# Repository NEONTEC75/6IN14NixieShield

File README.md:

# 6IN14NixieShield
This shield is just a minimal Nixie multiplexed circuit and contains the following components:
- 74141 nixie cathode driver IC (pins 4, 6, 7, 5);
- TLP627 opto-couplers for anodes (pins 12, 11, 9, 8, A1, A2, and pin 10 for the dots);
- 3-button resistive keyboard (A3);
- simple boost converter driven by Arduino's PWM (pin 3, and pin A0 for output voltage feedback);
- DS3231 module connector.

The library with some examples:
https://github.com/NEONTEC75/Nixie6IN14

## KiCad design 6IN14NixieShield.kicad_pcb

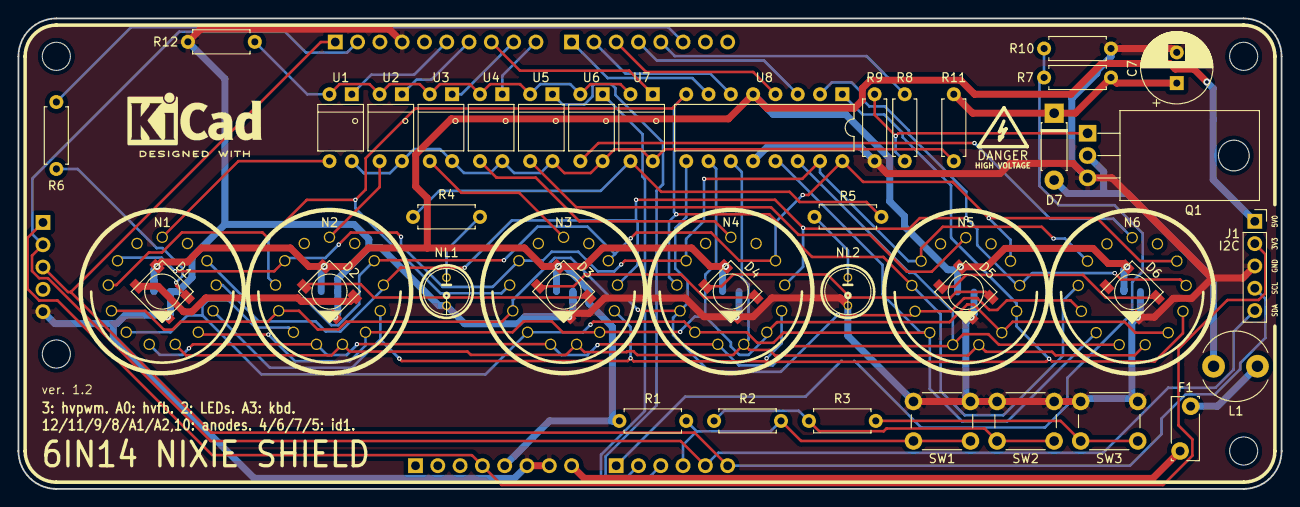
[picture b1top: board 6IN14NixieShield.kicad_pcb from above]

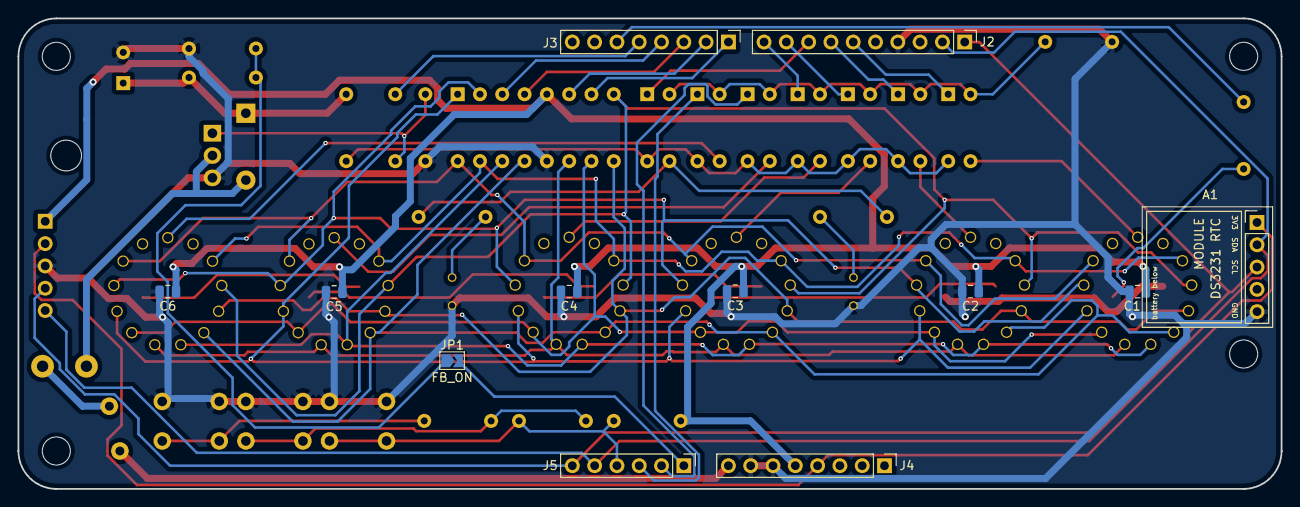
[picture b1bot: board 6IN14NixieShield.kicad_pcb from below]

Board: 2 copper layers, 143.9 x 53.6 mm, 61 parts (12 on the bottom side), 55 nets.

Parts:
A1: DS3231
C1, C2, C3, C4, C5, C6: 100n; C_0805_2012Metric
C7: 4.7uF*350V; CP_Radial_D8.0mm_P3.50mm
D1, D2, D3, D4, D5, D6: WS2812B
D7: HER106; D_DO-41_SOD81_P7.62mm_Horizontal
F1: 1A; Fuse_Bourns_MF-RG300
H1, H2, H3, H4: MountingHole; MountingHole_3.2mm_M3_DIN965
HVSIGN: Symbol_HighVoltage_Type2_SilkScreen_VerySmall
J1: I2C; PinSocket_1x05_P2.54mm_Vertical
J2: UNO3; PinHeader_1x10_P2.54mm_Vertical
J3: UNO4; PinHeader_1x08_P2.54mm_Vertical
J4: UNO1; PinHeader_1x08_P2.54mm_Vertical
J5: UNO2; PinHeader_1x06_P2.54mm_Vertical
JP1: FB_ON; SolderJumper-2_P1.3mm_Open_TrianglePad1.0x1.5mm
KICADLOGO: KiCad-Logo2_6mm_SilkScreen
L1: 470uH; L_Radial_D7.8mm_P5.00mm_Fastron_07HCP
N1, N2, N3, N4, N5, N6: IN-14; IN-14new
NL1, NL2: NeonLamp
Q1: IRF740; TO-220-3_Horizontal_TabDown
R1, R2, R3: 10k; R_Axial_DIN0207_L6.3mm_D2.5mm_P7.62mm_Horizontal
R4, R5, R10: 4k7; R_Axial_DIN0207_L6.3mm_D2.5mm_P7.62mm_Horizontal
R6: 100; R_Axial_DIN0207_L6.3mm_D2.5mm_P7.62mm_Horizontal
R7: 300k; R_Axial_DIN0207_L6.3mm_D2.5mm_P7.62mm_Horizontal
R8: 22; R_Axial_DIN0207_L6.3mm_D2.5mm_P7.62mm_Horizontal
R9: 100k; R_Axial_DIN0207_L6.3mm_D2.5mm_P7.62mm_Horizontal
R11: 2k2; R_Axial_DIN0207_L6.3mm_D2.5mm_P7.62mm_Horizontal
R12: 470; R_Axial_DIN0207_L6.3mm_D2.5mm_P7.62mm_Horizontal
SW1, SW2, SW3: SW_Push; SW_PUSH_6mm_H4.3mm
U1, U2, U3, U4, U5, U6, U7: TLP627
U8: K155ID1; DIP-16_W7.62mm

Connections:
+3V3: A1.1, J1.2, J4.4
+5V: C1.1, C2.1, C3.1, C4.1, C5.1, C6.1, D1.1, D2.1, D3.1, D4.1, D5.1, D6.1, J1.1, J4.5, R1.1, U8.5
/A0: J5.1, JP1.2
/A1: J5.2, U5.1
/A2: J5.3, U6.1
/A3: J5.4, R1.2, R2.1, SW1.1
/A4: A1.2, J1.5, J2.2, J5.5
/A5: A1.3, J1.4, J2.1, J5.6
/BOOST_PWM: J3.5, R8.2
/CTL_A1: J2.6, U1.1
/CTL_A2: J2.7, U2.1
/CTL_A3: J2.9, U3.1
/CTL_A4: J2.10, U4.1
/CTL_Adots: J2.8, U7.1
/D2: J3.6, R6.1
/D4: J3.4, U8.3
/D5: J3.3, U8.4
/D6: J3.2, U8.6
/D7: J3.1, U8.7
/NixieCtl/+HV: C7.1, D7.1, R7.2, R11.1
/NixieCtl/ANODE_1: N1.A, U1.3
/NixieCtl/ANODE_2: N2.A, U2.3
/NixieCtl/ANODE_3: N3.A, U3.3
/NixieCtl/ANODE_4: N4.A, U4.3
/NixieCtl/ANODE_5: N5.A, U5.3
/NixieCtl/ANODE_6: N6.A, U6.3
/NixieCtl/CATHODE_0: N1.0, N2.0, N3.0, N4.0, N5.0, N6.0, U8.16
/NixieCtl/CATHODE_1: N1.1, N2.1, N3.1, N4.1, N5.1, N6.1, U8.15
/NixieCtl/CATHODE_2: N1.2, N2.2, N3.2, N4.2, N5.2, N6.2, U8.8
/NixieCtl/CATHODE_3: N1.3, N2.3, N3.3, N4.3, N5.3, N6.3, U8.9
/NixieCtl/CATHODE_4: N1.4, N2.4, N3.4, N4.4, N5.4, N6.4, U8.13
/NixieCtl/CATHODE_5: N1.5, N2.5, N3.5, N4.5, N5.5, N6.5, U8.14
/NixieCtl/CATHODE_6: N1.6, N2.6, N3.6, N4.6, N5.6, N6.6, U8.11
/NixieCtl/CATHODE_7: N1.7, N2.7, N3.7, N4.7, N5.7, N6.7, U8.10
/NixieCtl/CATHODE_8: N1.8, N2.8, N3.8, N4.8, N5.8, N6.8, U8.1
/NixieCtl/CATHODE_9: N1.9, N2.9, N3.9, N4.9, N5.9, N6.9, U8.2
/Tubes/ANODE_DOTS: R4.2, R5.2, U7.3
/VIN: F1.1, J4.8
GND: A1.5, C1.2, C2.2, C3.2, C4.2, C5.2, C6.2, C7.2, D1.3, D2.3, D3.3, D4.3, D5.3, D6.3, J1.3, J2.4, J4.6, J4.7, NL1.2, NL2.2, Q1.3, R9.2, R10.1, R12.2, SW1.2, SW2.2, SW3.2, U8.12
unnamed: D1.2, D2.4
unnamed: D1.4, R6.2
unnamed: D2.2, D3.4
unnamed: D3.2, D4.4
unnamed: D4.2, D5.4
unnamed: D5.2, D6.4
unnamed: D7.2, L1.1, Q1.2
unnamed: F1.2, L1.2
unnamed: JP1.1, R7.1, R10.2
unnamed: NL1.1, R4.1
unnamed: NL2.1, R5.1
unnamed: Q1.1, R8.1, R9.1
unnamed: R2.2, R3.1, SW2.1
unnamed: R3.2, SW3.1
unnamed: R11.2, U1.4, U2.4, U3.4, U4.4, U5.4, U6.4, U7.4
unnamed: R12.1, U1.2, U2.2, U3.2, U4.2, U5.2, U6.2, U7.2
